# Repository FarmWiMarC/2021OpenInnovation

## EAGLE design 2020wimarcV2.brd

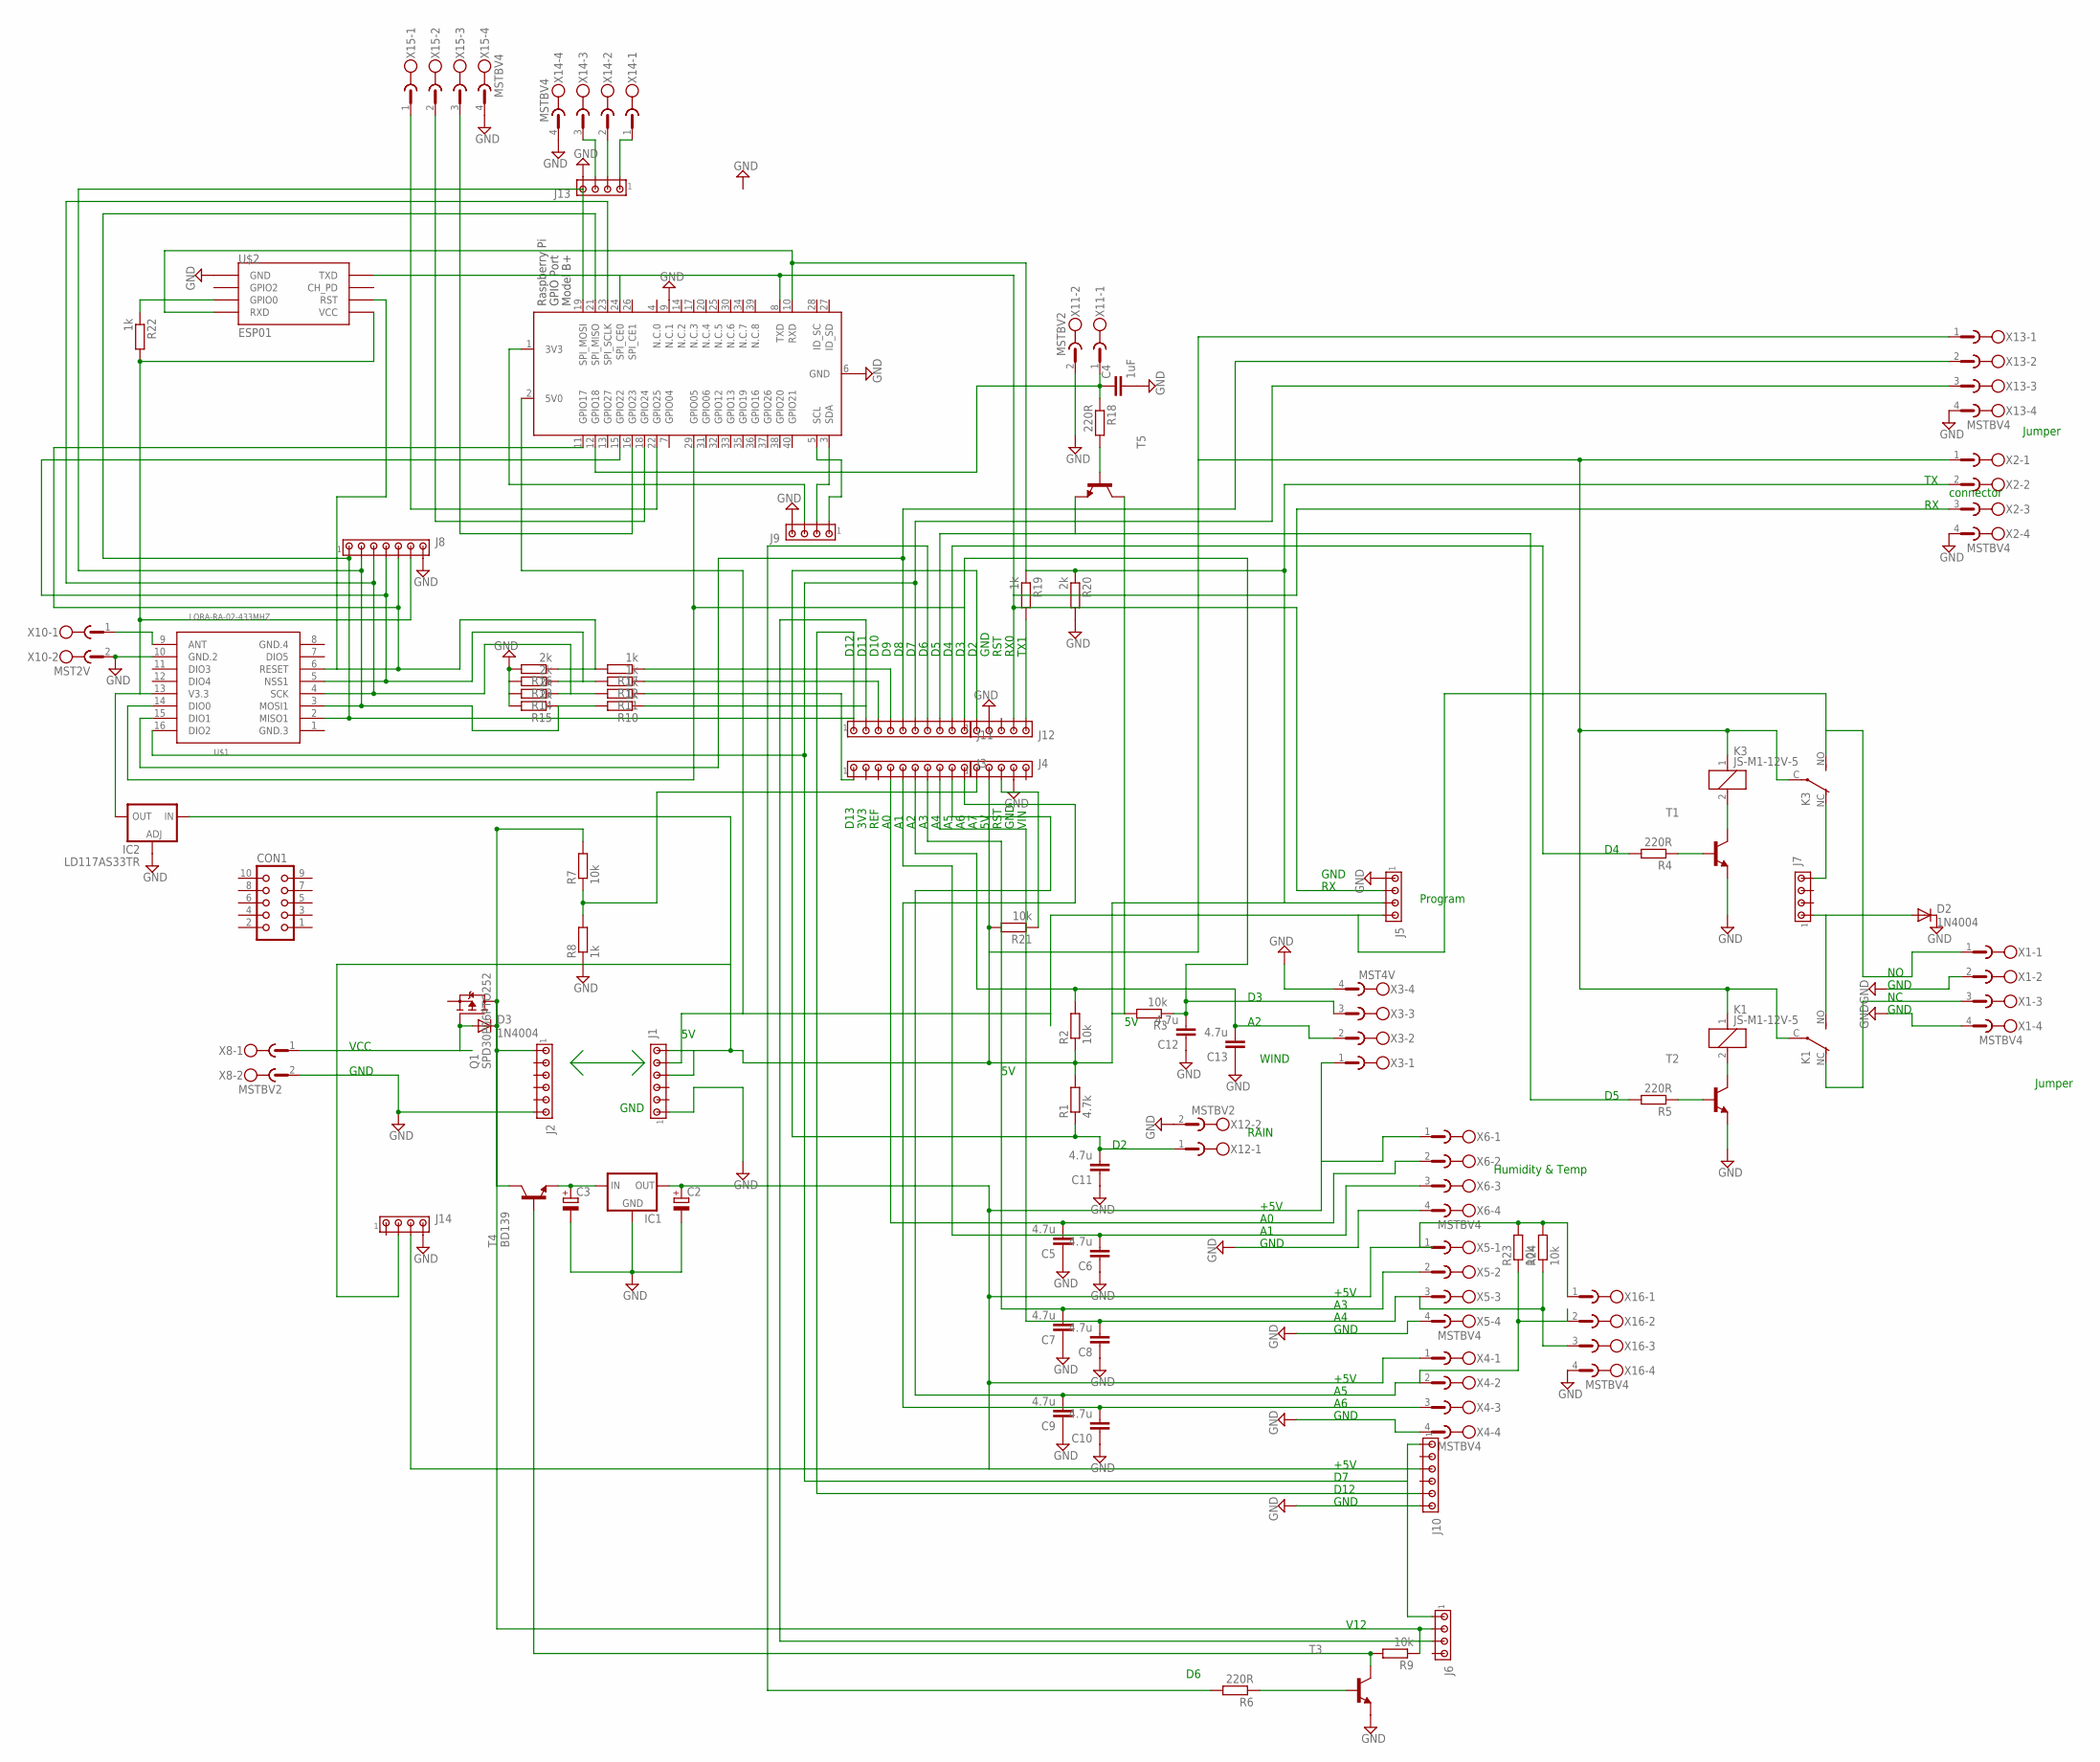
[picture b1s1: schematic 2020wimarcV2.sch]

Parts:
C2, C3: CPOL-EUE2.5-7; E2,5-7
C4: 1uF; C0805K
C5, C6, C7, C8, C9, C10, C11, C12, C13: 4.7u; C0805K
CON1: CON10
D2, D3: 1N4004; DO41-10
IC1: 78XXL
IC2: LD117AS33TR; SOT223
J1, J2, J10: MTA06-100; 10X06MTA
J3, J11: MTA10-100; 10X10MTA
J4, J12: MTA05-100; 10X05MTA
J5, J6, J7, J9, J13, J14: MTA04-100; 10X04MTA
J8: MTA07-100; 10X07MTA
K1, K3: JS-M1-12V-5; JS-M
Q1: SPD30P06PTO252; TO252
R1: 4.7k; M0805
R2, R3, R7, R9, R21, R23, R24: 10k; M0805
R4, R5, R6, R18: 220R; M0805
R8, R10, R11, R12, R17, R19, R22: 1k; M0805
R13, R14, R15, R16, R20: 2k; M0805
T1, T2, T3, T5: -NPN-SOT89-BCE; SOT89-BCE
T4: BD139; TO126
U$1: LORA-RA-02-433MHZ; LORA-RA2-SMD
U$2: ESP01
X1, X2, X4, X5, X6, X13, X14, X15, X16: MSTBV4
X3: MST4V; MSTBV4
X8, X11, X12: MSTBV2
X9: RASPI_BOARD_B+_F; RASPI_BOARD_B+_FULL
X10: MST2V; MSTBV2

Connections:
DIO3: U$1.11 (DIO3)
GND: C2.-, C3.-, C4.2, C5.1, C6.1, C7.1, C8.1, C9.1, C10.1, C11.1, C12.1, C13.1, D2.C, IC1.GND, IC2.1 (ADJ), J1.1, J2.6, J4.4, J5.1, J8.7, J9.4, J10.6, J12.2, J13.4, J14.4, R8.1, R13.2, R14.2, R15.2, R16.2, R20.2, T1.E, T2.E, T3.E, U$1.10 (GND.2), U$2.GND, X1.2, X1.4, X2.4, X3.4, X4.4, X5.4, X6.4, X8.2, X9.6 (GND), X9.9 (N.C.1), X10.2, X11.2, X12.2, X13.4, X14.4, X15.4, X16.4
GND.3: U$1.1 (GND.3)
GND.4: U$1.8 (GND.4)
unnamed: C5.2, J3.4, X6.2
unnamed: C11.2, J12.1, R1.1, X12.1
unnamed: C12.2, J11.10, R3.1, U$1.14 (DIO0), X3.3, X9.29 (GPIO05)
unnamed: C13.2, J3.6, R2.2, X3.2
unnamed: J7.4, K3.NC (O)
unnamed: J3.1, R11.1
unnamed: D3.A, Q1.1 (G), X8.1
unnamed: R19.1, R20.1, U$2.RX (RXD), X2.2, X9.10 (RXD)
unnamed: J5.2, J12.4, U$2.TX (TXD), X2.3, X9.8 (TXD)
unnamed: J13.1, X14.1
unnamed: J11.3, R12.1
unnamed: D3.C, J2.1, J6.2, Q1.3 (D), R7.2, R9.1, T4.2 (C)
unnamed: C6.2, J3.5, X6.3
unnamed: C7.2, J3.7, X5.2
unnamed: C8.2, J3.8, R24.1, X5.3, X16.3
unnamed: C10.2, J3.10, X4.3
unnamed: J11.6, U$1.16 (DIO2), X13.3
unnamed: J8.1, J10.5, J11.1, U$1.2 (MISO1), X9.21 (SPI_MISO)
unnamed: K3.2, T1.C
unnamed: X9.22 (GPIO25), X15.1
unnamed: R4.1, T1.B
unnamed: K1.2, T2.C
unnamed: R5.1, T2.B
unnamed: K1.NC (O), X1.3
unnamed: R9.2, T3.C, T4.3 (B)
unnamed: C2.+, IC1.OUT, J10.3, J14.3, R23.2, R24.2, X3.1, X4.1, X5.1, X6.1, X16.1
unnamed: J4.1, R7.1, R8.2
unnamed: R6.1, T3.B
unnamed: J11.9, R4.2
unnamed: J11.8, R5.2, T5.E
unnamed: J11.7, R6.2
unnamed: J6.1, J10.1
unnamed: J8.3, R11.2, R14.1, U$1.4 (SCK), X9.23 (SPI_SCLK)
unnamed: D2.A, J7.1, K1.NO (S)
unnamed: R18.2, T5.B
unnamed: C3.+, IC1.IN, T4.1 (E)
unnamed: X9.18 (GPIO24), X15.2
unnamed: J8.5, R16.1, R17.2, U$1.6 (RESET), U$2.RST, X9.11 (GPIO17)
unnamed: J11.5, U$1.15 (DIO1), X13.2
unnamed: J8.2, R10.2, R15.1, U$1.3 (MOSI1), X9.19 (SPI_MOSI)
unnamed: J11.4, R17.1
unnamed: C4.1, R18.1, X9.12 (GPIO18), X11.1
unnamed: U$1.9 (ANT), X10.1
unnamed: J8.4, R12.2, R13.1, U$1.5 (NSS1), X9.15 (GPIO22)
unnamed: J12.5, R19.2
unnamed: J4.3, R21.1
unnamed: J9.2, X9.3 (SDA)
unnamed: J9.1, X9.5 (SCL)
unnamed: IC2.4 (OUT), J8.6, R22.2, U$1.13 (V3.3), U$2.VCC
unnamed: IC2.3 (IN), J1.4, J1.6, J4.2, J5.3, J14.2, K1.1, K1.C, K3.1, K3.C, R1.2, R2.1, R3.2, R21.2, T5.C, X2.1, X13.1
unnamed: J13.2, X14.2
unnamed: J13.3, X14.3
unnamed: X9.16 (GPIO23), X15.3
unnamed: J6.3, J11.2, R10.1
unnamed: J9.3, X9.1 (3V3)
unnamed: R22.1, U$2.GPIO0
unnamed: C9.2, J3.9, R23.1, X4.2, X16.2
unnamed: J1.5, J5.4, K3.NO (S), X1.1, X9.2 (5V0)

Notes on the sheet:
D13
3V3
REF
RST
GND
VIN
TX1
RX0
D10
D11
D12
Program
WIND
RAIN
+5V
Humidity & Temp
Jumper
connector
VCC
V12

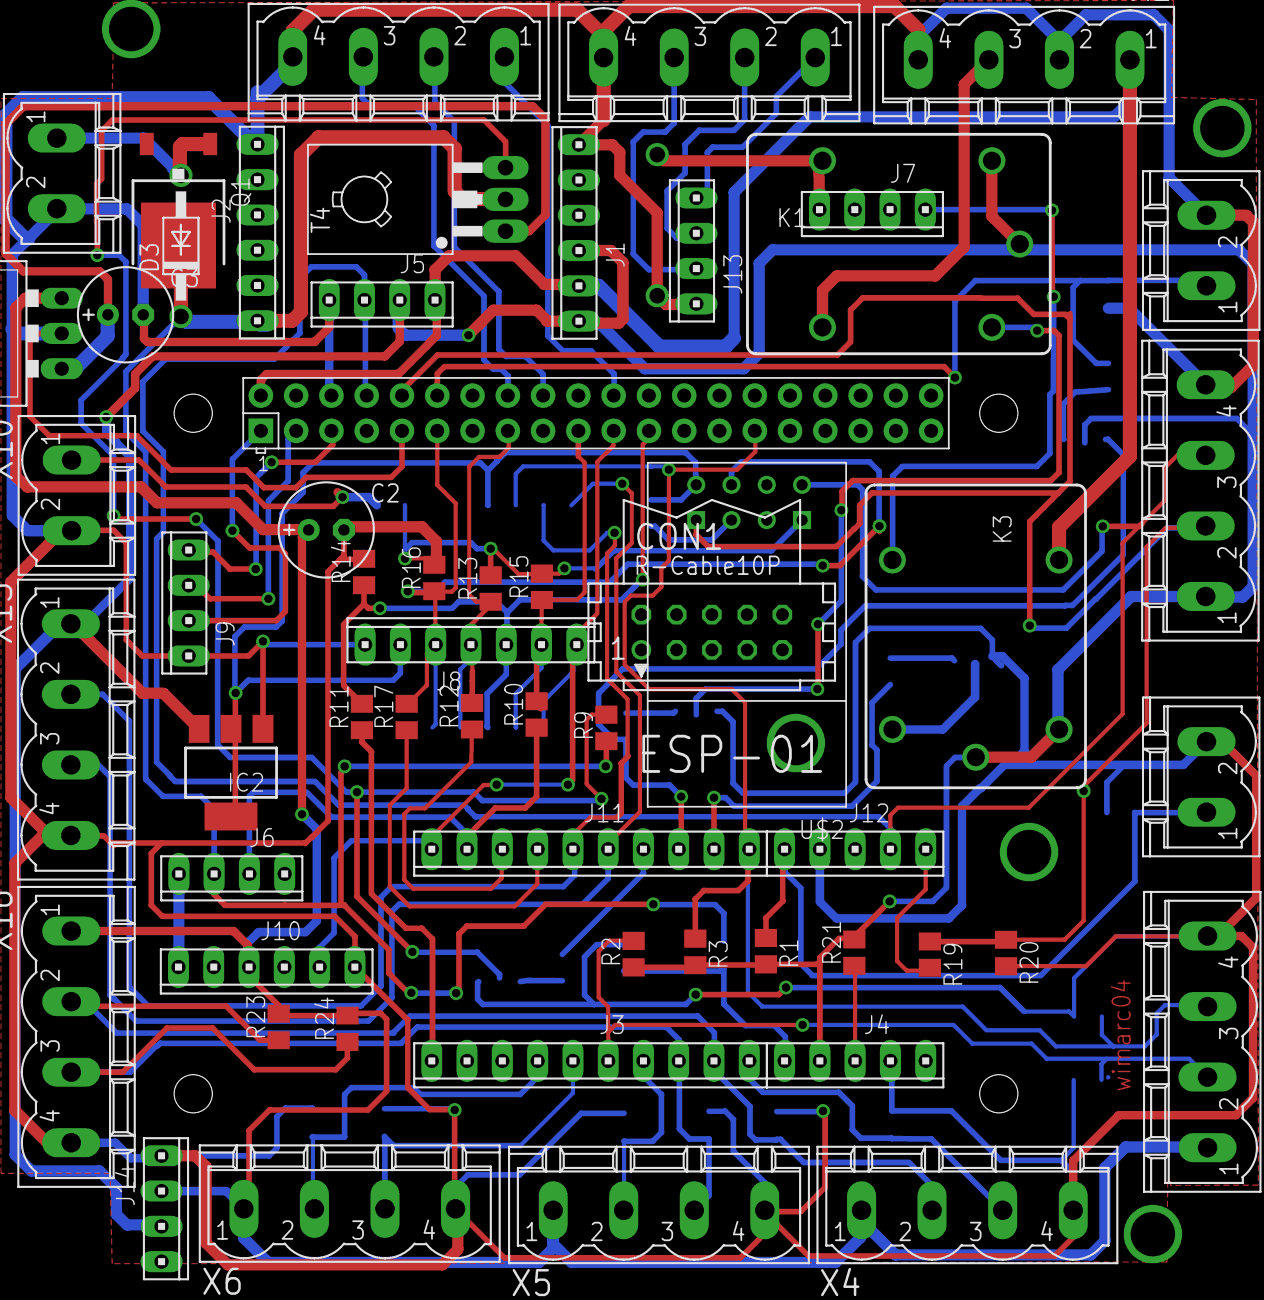
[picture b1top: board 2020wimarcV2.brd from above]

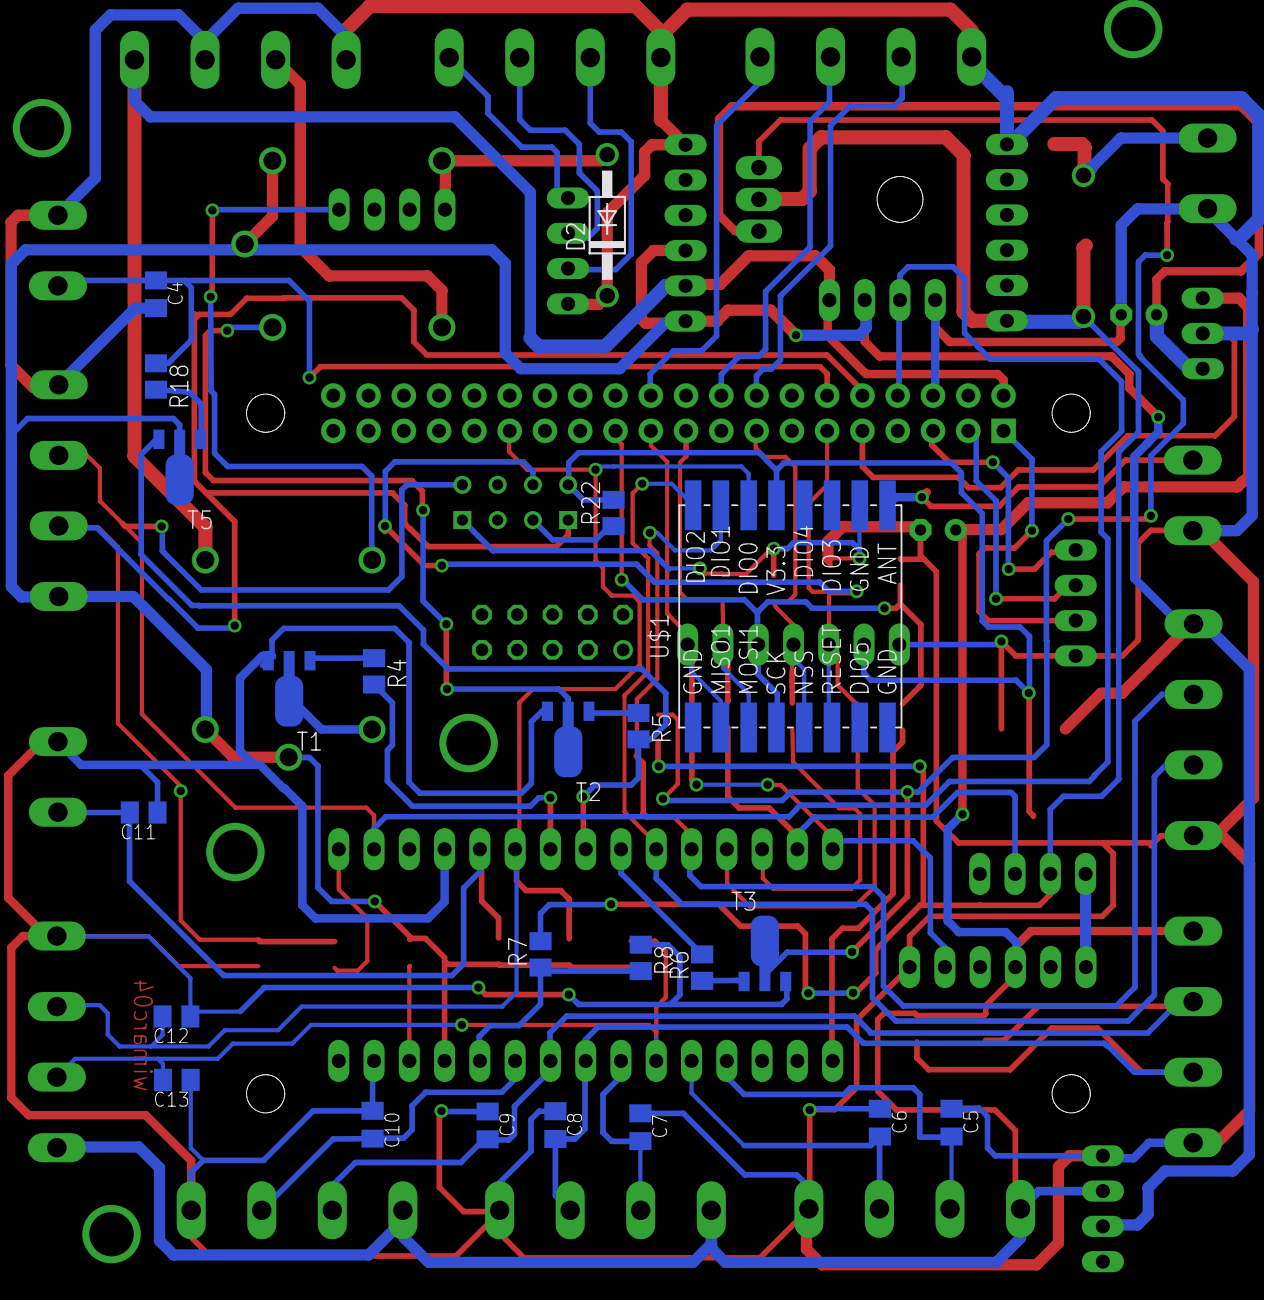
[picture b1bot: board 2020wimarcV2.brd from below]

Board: 2 copper layers, 80 parts (23 on the bottom side), 59 nets.
